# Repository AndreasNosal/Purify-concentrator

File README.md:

# Purify-concentrator
This device is designed to monitor and detect air quality at regular intervals, providing alerts when pollution levels become too high—prompting you to take action, such as opening a window. Ideal for indoor environments like homes, schools, or offices, it operates efficiently with a solar power input ranging from 5 to 16V.

Originally designed for: Young Energy Europe AHK Slowakei 
Link: https://slowakei.ahk.de/de

# License
 - Under GPL-3.0 license

# Use in action

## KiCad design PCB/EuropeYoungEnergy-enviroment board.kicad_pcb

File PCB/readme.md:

# Starter-Friendly Electrical Design for DIY Assembly

This project is an electrical design crafted to be accessible for **beginners**. It employs **through-hole components (THD)**, making it easy to assemble with a standard soldering iron. All complex circuitry is integrated into modules that mount directly onto the main PCB, eliminating the need for surface-mount devices (SMD) and simplifying the soldering process.

## Features

- **Overvoltage Protection**: Prevents damage from voltage spikes.
- **Reverse Voltage Protection**: Guards against incorrect polarity connections.
- **Active Buzzer & LED Indicators**: Provides clear audio and visual feedback.
- **Energy-Efficient Components**: Designed to conserve power.
- **Flexible Input Voltage (5-16V)**: Compatible with a range of sources, including solar panels.
- **Microcontroller Reset Button**: Convenient reset for the ESP32 microcontroller.
- **Input Power Options**: Supports both DC barrel jack and PH2 connectors.

## PCB Specifications

- **4-Layer PCB**
- **Dimensions**: 100x100 mm
- **Manufacturing**: Gerber files are available in the `gerber` directory, ready for JLCPCB.

[yee_diagram.pdf](https://github.com/user-attachments/files/17554162/yee_diagram.pdf)

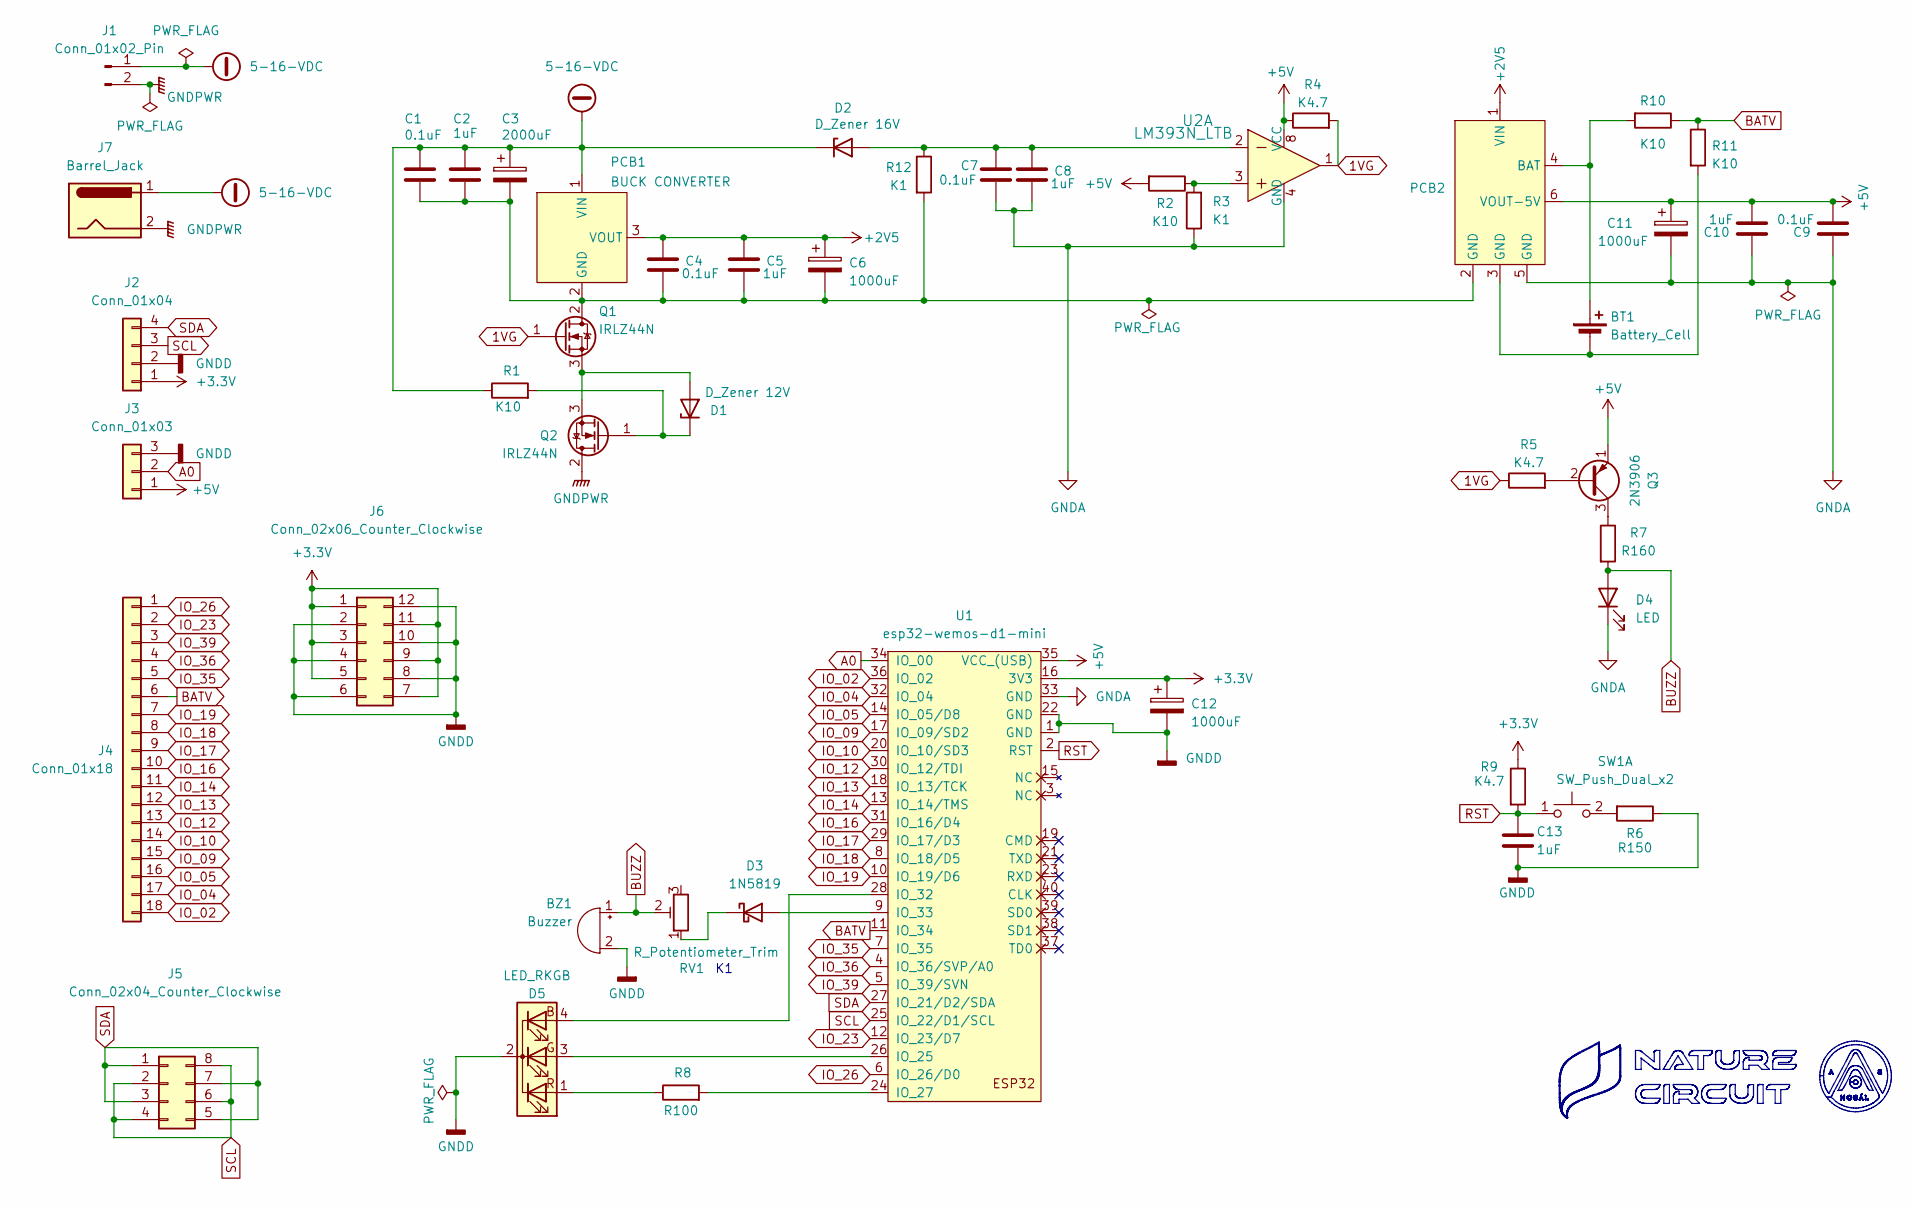
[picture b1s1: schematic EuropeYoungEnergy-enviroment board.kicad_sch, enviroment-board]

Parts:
BT1: Battery_Cell; BatteryHolder_MPD_BH-18650-PC2
BZ1: Buzzer; Buzzer_12x9.5RM7.6
C1, C4, C7, C9: 0.1uF; C_Disc_D4.3mm_W1.9mm_P5.00mm
C2, C5, C8, C10, C13: 1uF; C_Disc_D4.3mm_W1.9mm_P5.00mm
C3: 2000uF; CP_Radial_D12.5mm_P5.00mm
C6, C11, C12: 1000uF; CP_Radial_D12.5mm_P5.00mm
D1: D_Zener 12V; D_A-405_P10.16mm_Horizontal
D2: D_Zener 16V; D_A-405_P7.62mm_Horizontal
D3: 1N5819; D_A-405_P7.62mm_Horizontal
D4: LED; LED_D5.0mm
D5: LED_RKGB; RGB_LED
J1: Conn_01x02_Pin; JST_PH_B2B-PH-K_1x02_P2.00mm_Vertical
J2: Conn_01x04; PinHeader_1x04_P2.54mm_Vertical
J3: Conn_01x03; PinHeader_1x03_P2.54mm_Vertical
J4: Conn_01x18; PinHeader_1x18_P2.54mm_Vertical
J5: Conn_02x04_Counter_Clockwise; PinHeader_2x04_P2.54mm_Vertical
J6: Conn_02x06_Counter_Clockwise; PinHeader_2x06_P2.54mm_Vertical
J7: Barrel_Jack; Barrel_Jack_5.5mmODx2.1mmID_PJ-202A
PCB1: BUCK CONVERTER; TZT_4A_Mini_DC_DC_Buck_Converter
PCB2: MH_CD42_Charge_Discharge_Module
Q1, Q2: IRLZ44N; TO-220-3_Vertical
Q3: 2N3906; TO-92_Inline
R1, R2, R10, R11: K10; R_Axial_DIN0207_L6.3mm_D2.5mm_P10.16mm_Horizontal
R3, R12: K1; R_Axial_DIN0207_L6.3mm_D2.5mm_P10.16mm_Horizontal
R4, R5, R9: K4.7; R_Axial_DIN0207_L6.3mm_D2.5mm_P10.16mm_Horizontal
R6: R150; R_Axial_DIN0207_L6.3mm_D2.5mm_P10.16mm_Horizontal
R7: R160; R_Axial_DIN0207_L6.3mm_D2.5mm_P10.16mm_Horizontal
R8: R100; R_Axial_DIN0207_L6.3mm_D2.5mm_P10.16mm_Horizontal
RV1: R_Potentiometer_Trim; Potentiometer_Bourns_3296W_Vertical
SW1: SW_Push_Dual_x2; SW_SPST_Omron_B3F-40xx
U1: esp32-wemos-d1-mini
U2: LM393N_LTB; DIP-8_W7.62mm; MPN LM393N; Digi-Key_PN LM393NFS-ND

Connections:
1VG: Q1.1 (G), R4.2, R5.1, U2.1
5-16-VDC: C1.1, C2.1, C3.1, D2.1 (K), J1.1, J7.1, PCB1.1 (VIN), R1.1
+2V5: C4.1, C5.1, C6.1, PCB1.3 (VOUT), PCB2.1 (VIN)
+3.3V: C12.1, J2.1, J6.1, J6.3, J6.5, J6.7, J6.9, J6.11, R9.1, U1.16 (3V3)
+5V: C9.2, C10.2, C11.1, J3.1, PCB2.6 (VOUT-5V), Q3.1 (E), R2.2, R4.1, U1.35 (VCC_(USB)), U2.8 (VCC)
A0: J3.2, U1.34 (IO_00)
BATV: J4.6, R10.1, R11.1, U1.11 (IO_34)
BUZZ: BZ1.1 (+), D4.2 (A), R7.2, RV1.2
GNDA: C7.2, C8.2, C9.1, C10.1, C11.2, D4.1 (K), PCB2.5 (GND), R3.1, U1.33 (GND), U2.4 (GND)
GNDD: BZ1.2 (-), C12.2, C13.2, D5.2 (K), J2.2, J3.3, J6.2, J6.4, J6.6, J6.8, J6.10, J6.12, R6.1, U1.1 (GND), U1.22 (GND)
GNDPWR: J1.2, J7.2, Q2.2 (D)
IO_02: J4.18, U1.36 (IO_02)
IO_04: J4.17, U1.32 (IO_04)
IO_05: J4.16, U1.14 (IO_05/D8)
IO_09: J4.15, U1.17 (IO_09/SD2)
IO_10: J4.14, U1.20 (IO_10/SD3)
IO_12: J4.13, U1.30 (IO_12/TDI)
IO_13: J4.12, U1.18 (IO_13/TCK)
IO_14: J4.11, U1.13 (IO_14/TMS)
IO_16: J4.10, U1.31 (IO_16/D4)
IO_17: J4.9, U1.29 (IO_17/D3)
IO_18: J4.8, U1.8 (IO_18/D5)
IO_19: J4.7, U1.10 (IO_19/D6)
IO_23: J4.2, U1.12 (IO_23/D7)
IO_26: J4.1, U1.6 (IO_26/D0)
IO_35: J4.5, U1.7 (IO_35)
IO_36: J4.4, U1.4 (IO_36/SVP/A0)
IO_39: J4.3, U1.5 (IO_39/SVN)
unnamed: BT1.1 (+), PCB2.4 (BAT), R10.2
unnamed: BT1.2 (-), PCB2.3 (GND), R11.2
unnamed: D1.2 (A), Q1.3 (S), Q2.3 (S)
unnamed: D1.1 (K), Q2.1 (G), R1.2
unnamed: C7.1, C8.1, D2.2 (A), R12.1, U2.2
unnamed: D3.2 (A), U1.9 (IO_33)
unnamed: D3.1 (K), RV1.1
unnamed: D5.4 (BA), U1.28 (IO_32)
unnamed: D5.3 (GA), U1.26 (IO_25)
unnamed: D5.1 (RA), R8.1
unnamed: C1.2, C2.2, C3.2, C4.2, C5.2, C6.2, PCB1.2 (GND), PCB2.2 (GND), Q1.2 (D), R12.2
unnamed: Q3.2 (B), R5.2
unnamed: Q3.3 (C), R7.1
unnamed: R2.1, R3.2, U2.3
unnamed: R6.2, SW1.2 (D)
unnamed: R8.2, U1.24 (IO_27)
RST: C13.1, R9.2, SW1.1 (C), U1.2 (RST)
SCL: J2.3, J5.2, J5.4, J5.6, J5.8, U1.25 (IO_22/D1/SCL)
SDA: J2.4, J5.1, J5.3, J5.5, J5.7, U1.27 (IO_21/D2/SDA)

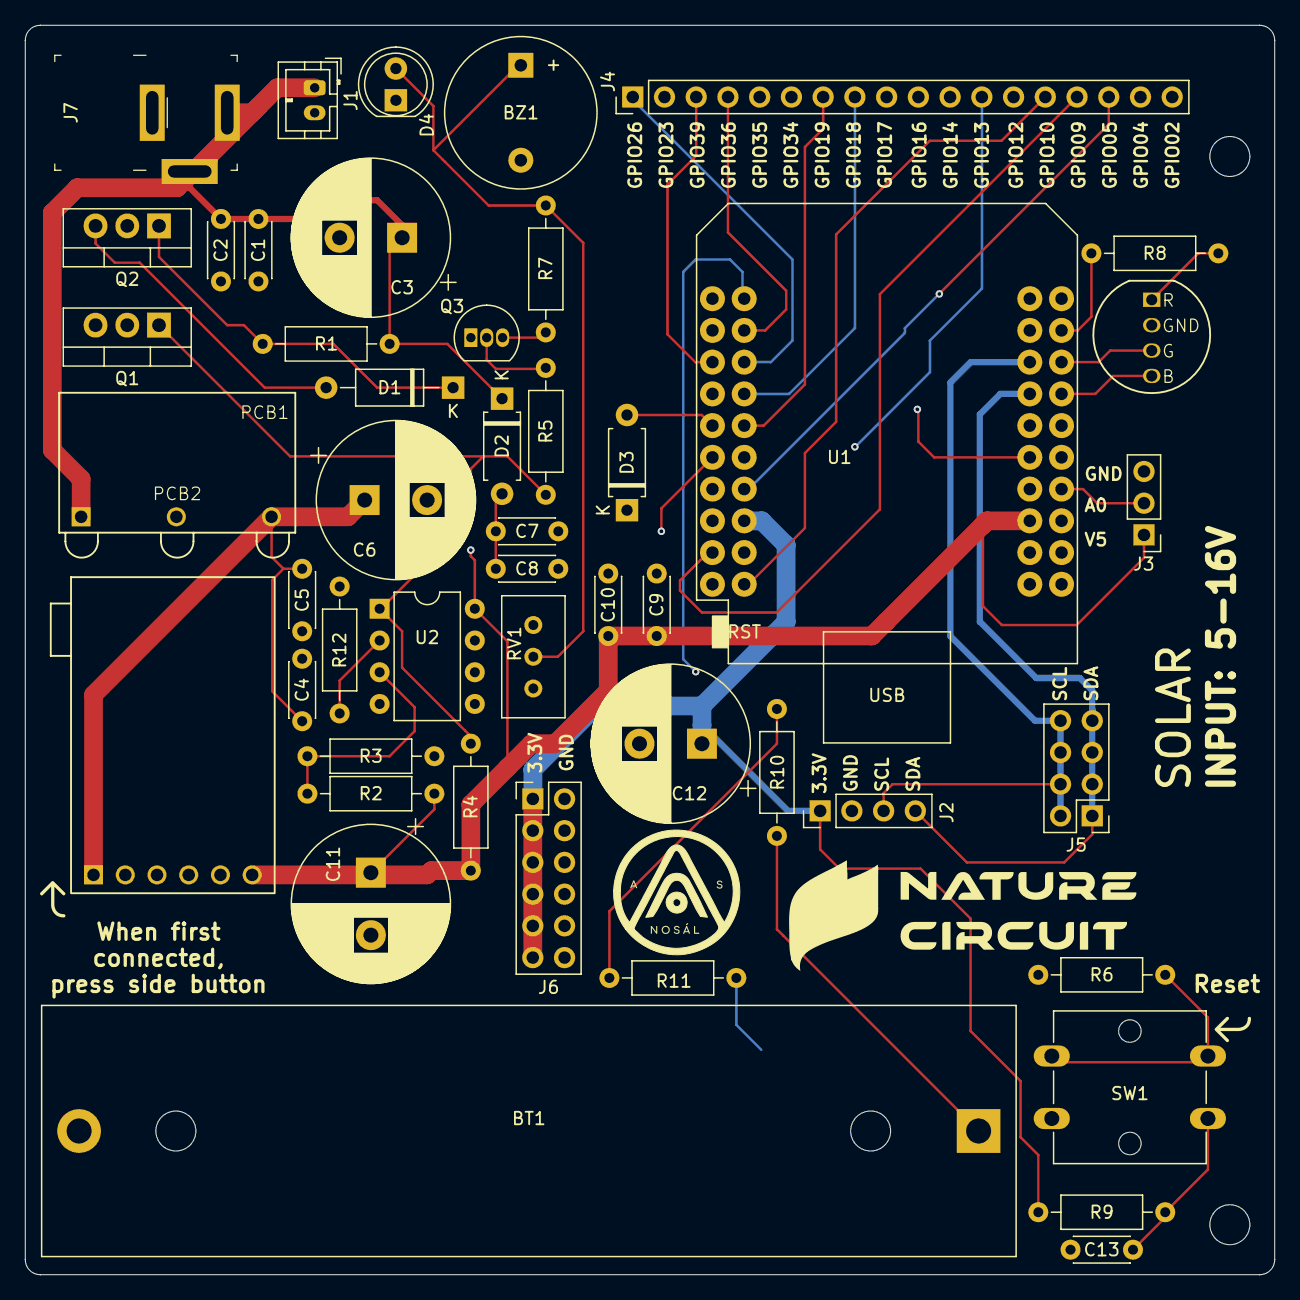
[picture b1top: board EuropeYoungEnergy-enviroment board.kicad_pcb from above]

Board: 4 copper layers, 100.0 x 100.0 mm, 48 parts (0 on the bottom side), 47 nets.

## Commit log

2024-10-24 add code for device
2024-10-29 Added kicad files - version 8.0
2024-10-29 Added zip gerber
    Files for JLCPCB manufacturing
2024-10-29 Added 3D files
2024-10-29 Move file into code
2024-10-29 Update readme.md for circuitry
2024-10-29 Update time cycle
2024-10-29 Update readme.md for code section
2024-11-02 added bigger interval for BME680, changed battery minimum votlage
    interval for BME680 changed from 30 seconds to 120 seconds.
    Minimum battery voltage to 3.15. Even if it's not the minimum voltage for lithium battery, the charging circuit is set to that minimum. After this minimum is passed, the microcontroller deepsleeps fo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
